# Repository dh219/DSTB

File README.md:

## David's ST Booster (DSTB)

# WARNING 27 July 2024 #

I strongly recommend no new builds of this project for now. I believe there's a reliabiltiy of executing from AltRAM which I've not been able to get to the bottom of.

Memory tests pass reliably, but I think the approach to this design in combination with clock switching and attempting to service DMA is inherently flawed.

Unless I find a firmware fix, in which case I'll log that here, I recommend persuing other designs or waiting for a revision 2.

David.

---

#### A low-cost DIY 16MHz 68000 accelerator with 8MB fast AltRAM and optional ROM cacheing

Fitting into a small footprint, just 3mm wider than the 68000 socket into which this plugs, the board (\~$4) contains one XC95144XL-100 CPLD (\~$5), one 32Mbit TSSOP-II-54 SDRAM chip (~$5), two level-shifting buffers (\~$6), one 5 or 3.3V 66MHz oscillator in a 7x5mm package (\~$4) and a 3.3V LDO voltage regulator (\~$2) as the core components.

This provides all the interface between the ST and a 16MHz capable 68000. The 68000 will run at the oscillator frequency divided by four, so 16.5MHz in normal configuration.

The AltRAM runs at at full speed for a 16MHz processor, offering throughput of around 7.7MB/s compared to ST-RAM's 3.7MB/s.

Firmware source (ISE), board design files (KiCAD) and any source for support programs will be published at each release.

#### Cost & requirements

I anticipate a single board can be hand assembled for approximately 30USD. You may need to acquire a 16MHz capable DIP-64 68000 to pair with it if your old 8MHz chip cannot handle the faster clock.

#### Manual

At the moment, there is no manual. This will be written in due course.

There is a build video available at https://youtu.be/VHx3kat0Q6M

### Resistor Networks

All resistor networks are recommended, however if you have already carried out preventative maintenance on your ST board such that the bus resistor packs have been changed to 2k2 or lower, you may omit the resistor packs on the address and data bus (RN1-10).

Please note, RN11 is not a supplementary bus pull-up pack and is required for correct operation of the firmware.

#### Software

See https://github.com/dh219/DSTB-tools for the 'AltRAM' or 'AltROM' programs (NB. 'AltROM' hasn't been properly tested with later firmware builds & this board is not compatible with 'ExxosRAM.PRG').

EmuTOS automatically recognises and activate AltRAM.

---

*Copyright 2022 D Henderson, released under GPL2.0*

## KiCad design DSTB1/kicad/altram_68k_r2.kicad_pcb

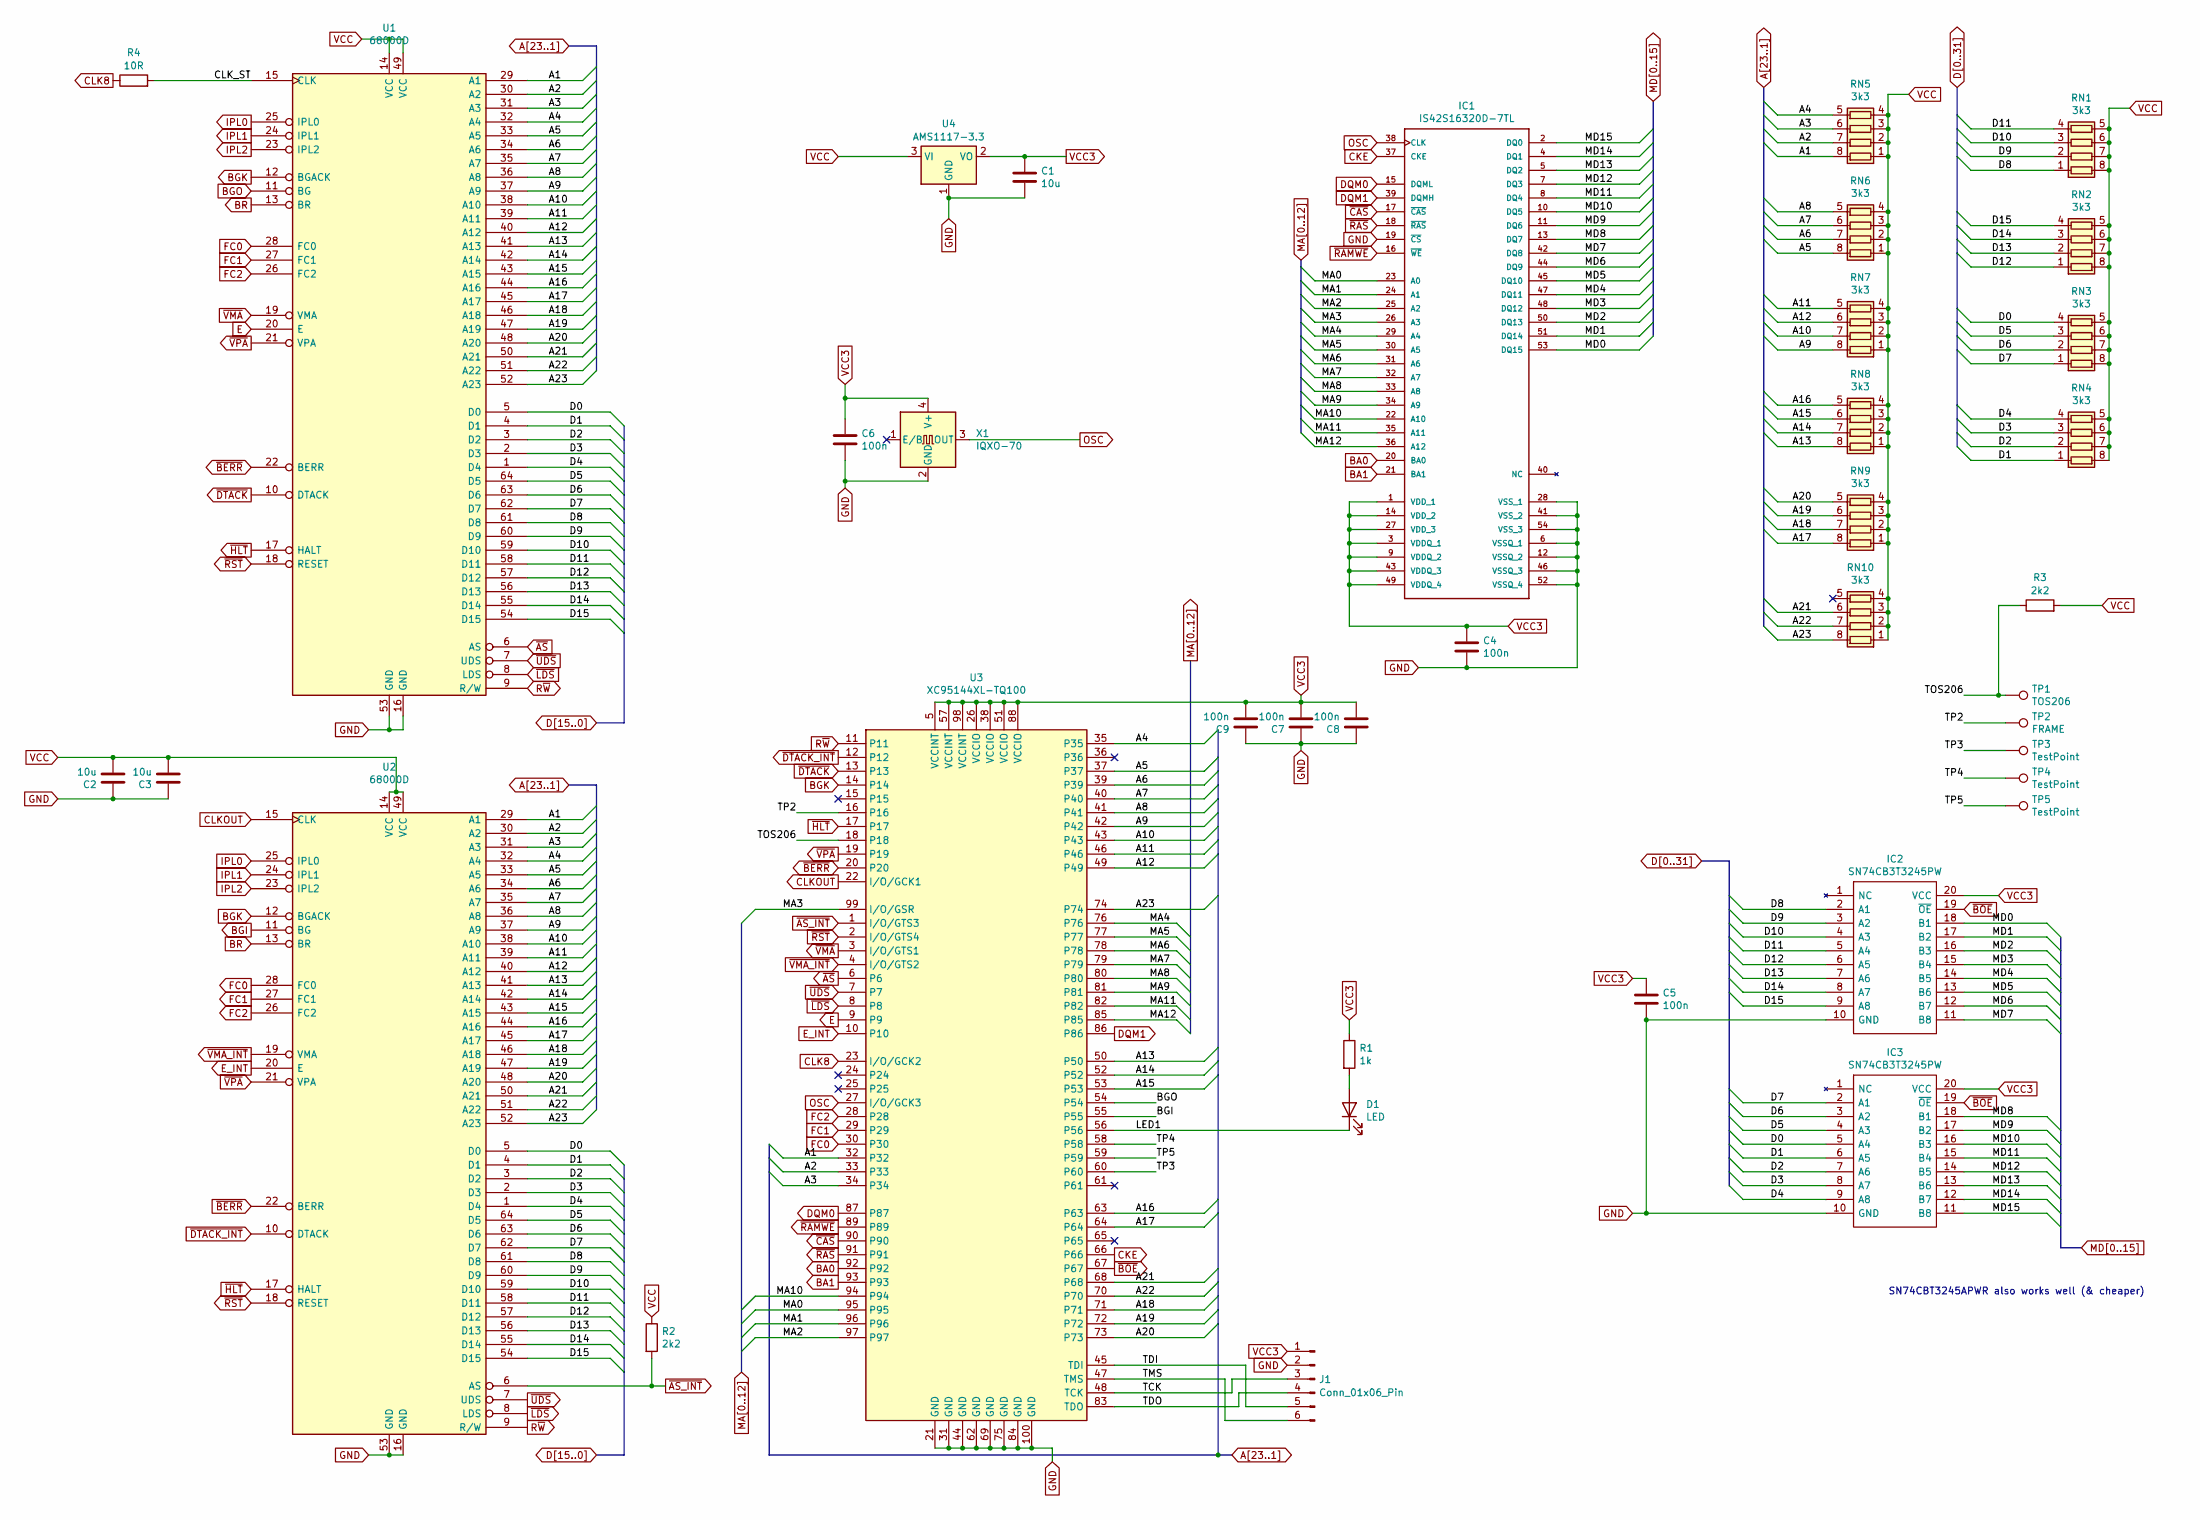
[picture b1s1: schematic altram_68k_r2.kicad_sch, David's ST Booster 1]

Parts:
C1, C2, C3: 10u; C_0805_2012Metric_Pad1.18x1.45mm_HandSolder
C4, C5, C6, C7, C8, C9: 100n; C_0805_2012Metric_Pad1.18x1.45mm_HandSolder
D1: LED; LED_0805_2012Metric_Pad1.15x1.40mm_HandSolder
IC1: IS42S16320D-7TL; TSOP-II-54_22.2x10.16mm_P0.8mm; MANUFACTURER_PART_NUMBER IS42S16320D-7TL
IC2, IC3: SN74CB3T3245PW; TSSOP-20_4.4x6.5mm_P0.65mm; Manufacturer_Part_Number SN74CB3T3245DW; Mouser Part Number 595-SN74CB3T3245DW
J1: Conn_01x06_Pin; PinHeader_1x06_P2.54mm_Horizontal
R1: 1k; R_0805_2012Metric_Pad1.20x1.40mm_HandSolder
R2, R3: 2k2; R_0805_2012Metric_Pad1.20x1.40mm_HandSolder
R4: 10R; R_0805_2012Metric_Pad1.20x1.40mm_HandSolder
RN1, RN2, RN3, RN4, RN5, RN6, RN7, RN8, RN9, RN10: 3k3; R_Array_Convex_4x0603
TP1: TOS206; TestPoint_THTPad_1.0x1.0mm_Drill0.5mm
TP2: FRAME; TestPoint_THTPad_1.0x1.0mm_Drill0.5mm
TP3, TP4, TP5: TestPoint; TestPoint_THTPad_1.0x1.0mm_Drill0.5mm
U1: 68000D; DIP-64_W22.86mm
U2: 68000D; DIP-64_W22.86mm_Socket
U3: XC95144XL-TQ100; TQFP-100_14x14mm_P0.5mm
U4: AMS1117-3.3; SOT-223-3_TabPin2
X1: IQXO-70; Oscillator_SMD_IQD_IQXO70-4Pin_7.5x5.0mm

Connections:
/CLK_ST: R4.2, U1.15 (CLK)
/LED1: D1.1 (K), U3.56
/TCK: J1.3, U3.48 (TCK)
/TDI: J1.5, U3.45 (TDI)
/TDO: J1.4, U3.83 (TDO)
/TMS: J1.6, U3.47 (TMS)
/TOS206: R3.1, TP1.1, U3.18
/TP2: TP2.1, U3.16
/TP3: TP3.1, U3.60
/TP4: TP4.1, U3.58
/TP5: TP5.1, U3.59
A1: RN5.8 (R1.2), U1.29 (A1), U2.29 (A1), U3.32
A2: RN5.7 (R2.2), U1.30 (A2), U2.30 (A2), U3.33
A3: RN5.6 (R3.2), U1.31 (A3), U2.31 (A3), U3.34
A4: RN5.5 (R4.2), U1.32 (A4), U2.32 (A4), U3.35
A5: RN6.8 (R1.2), U1.33 (A5), U2.33 (A5), U3.37
A6: RN6.7 (R2.2), U1.34 (A6), U2.34 (A6), U3.39
A7: RN6.6 (R3.2), U1.35 (A7), U2.35 (A7), U3.40
A8: RN6.5 (R4.2), U1.36 (A8), U2.36 (A8), U3.41
A9: RN7.8 (R1.2), U1.37 (A9), U2.37 (A9), U3.42
A10: RN7.7 (R2.2), U1.38 (A10), U2.38 (A10), U3.43
A11: RN7.5 (R4.2), U1.39 (A11), U2.39 (A11), U3.46
A12: RN7.6 (R3.2), U1.40 (A12), U2.40 (A12), U3.49
A13: RN8.8 (R1.2), U1.41 (A13), U2.41 (A13), U3.50
A14: RN8.7 (R2.2), U1.42 (A14), U2.42 (A14), U3.52
A15: RN8.6 (R3.2), U1.43 (A15), U2.43 (A15), U3.53
A16: RN8.5 (R4.2), U1.44 (A16), U2.44 (A16), U3.63
A17: RN9.8 (R1.2), U1.45 (A17), U2.45 (A17), U3.64
A18: RN9.7 (R2.2), U1.46 (A18), U2.46 (A18), U3.71
A19: RN9.6 (R3.2), U1.47 (A19), U2.47 (A19), U3.72
A20: RN9.5 (R4.2), U1.48 (A20), U2.48 (A20), U3.73
A21: RN10.6 (R3.2), U1.50 (A21), U2.50 (A21), U3.68
A22: RN10.7 (R2.2), U1.51 (A22), U2.51 (A22), U3.70
A23: RN10.8 (R1.2), U1.52 (A23), U2.52 (A23), U3.74
BA0: IC1.20 (BA0), U3.92
BA1: IC1.21 (BA1), U3.93
BGI: U2.11 (BG), U3.55
BGK: U1.12 (BGACK), U2.12 (BGACK), U3.14
BGO: U1.11 (BG), U3.54
BR: U1.13 (BR), U2.13 (BR)
CKE: IC1.37 (CKE), U3.66
CLK8: R4.1, U3.23 (I/O/GCK2)
CLKOUT: U2.15 (CLK), U3.22 (I/O/GCK1)
D0: IC3.5 (A4), RN3.4 (R4.1), U1.5 (D0), U2.5 (D0)
D1: IC3.6 (A5), RN4.1 (R1.1), U1.4 (D1), U2.4 (D1)
D2: IC3.7 (A6), RN4.2 (R2.1), U1.3 (D2), U2.3 (D2)
D3: IC3.8 (A7), RN4.3 (R3.1), U1.2 (D3), U2.2 (D3)
D4: IC3.9 (A8), RN4.4 (R4.1), U1.1 (D4), U2.1 (D4)
D5: IC3.4 (A3), RN3.3 (R3.1), U1.64 (D5), U2.64 (D5)
D6: IC3.3 (A2), RN3.2 (R2.1), U1.63 (D6), U2.63 (D6)
D7: IC3.2 (A1), RN3.1 (R1.1), U1.62 (D7), U2.62 (D7)
D8: IC2.2 (A1), RN1.1 (R1.1), U1.61 (D8), U2.61 (D8)
D9: IC2.3 (A2), RN1.2 (R2.1), U1.60 (D9), U2.60 (D9)
D10: IC2.4 (A3), RN1.3 (R3.1), U1.59 (D10), U2.59 (D10)
D11: IC2.5 (A4), RN1.4 (R4.1), U1.58 (D11), U2.58 (D11)
D12: IC2.6 (A5), RN2.1 (R1.1), U1.57 (D12), U2.57 (D12)
D13: IC2.7 (A6), RN2.2 (R2.1), U1.56 (D13), U2.56 (D13)
D14: IC2.8 (A7), RN2.3 (R3.1), U1.55 (D14), U2.55 (D14)
D15: IC2.9 (A8), RN2.4 (R4.1), U1.54 (D15), U2.54 (D15)
DQM0: IC1.15 (DQML), U3.87
DQM1: IC1.39 (DQMH), U3.86
E: U1.20 (E), U3.9
E_INT: U2.20 (E), U3.10
FC0: U1.28 (FC0), U2.28 (FC0), U3.30
FC1: U1.27 (FC1), U2.27 (FC1), U3.29
FC2: U1.26 (FC2), U2.26 (FC2), U3.28
GND: C1.2, C2.1, C3.1, C4.2, C5.2, C6.2, C7.1, C8.1, C9.1, IC1.6 (VSSQ_1), IC1.12 (VSSQ_2), IC1.19 (~CS), IC1.28 (VSS_1), IC1.41 (VSS_2), IC1.46 (VSSQ_3), IC1.52 (VSSQ_4), IC1.54 (VSS_3), IC2.10 (GND), IC3.10 (GND), J1.2, U1.16 (GND), U1.53 (GND), U2.16 (GND), U2.53 (GND), U3.21 (GND), U3.31 (GND), U3.44 (GND), U3.62 (GND), U3.69 (GND), U3.75 (GND), U3.84 (GND), U3.100 (GND), U4.1 (GND), X1.2 (GND)
IPL0: U1.25 (IPL0), U2.25 (IPL0)
IPL1: U1.24 (IPL1), U2.24 (IPL1)
IPL2: U1.23 (IPL2), U2.23 (IPL2)
MA0: IC1.23 (A0), U3.95
MA1: IC1.24 (A1), U3.96
MA2: IC1.25 (A2), U3.97
MA3: IC1.26 (A3), U3.99 (I/O/GSR)
MA4: IC1.29 (A4), U3.76
MA5: IC1.30 (A5), U3.77
MA6: IC1.31 (A6), U3.78
MA7: IC1.32 (A7), U3.79
MA8: IC1.33 (A8), U3.80
MA9: IC1.34 (A9), U3.81
MA10: IC1.22 (A10), U3.94
MA11: IC1.35 (A11), U3.82
MA12: IC1.36 (A12), U3.85
MD0: IC1.53 (DQ15), IC2.18 (B1)
MD1: IC1.51 (DQ14), IC2.17 (B2)
MD2: IC1.50 (DQ13), IC2.16 (B3)
MD3: IC1.48 (DQ12), IC2.15 (B4)
MD4: IC1.47 (DQ11), IC2.14 (B5)
MD5: IC1.45 (DQ10), IC2.13 (B6)
MD6: IC1.44 (DQ9), IC2.12 (B7)
MD7: IC1.42 (DQ8), IC2.11 (B8)
MD8: IC1.13 (DQ7), IC3.18 (B1)
MD9: IC1.11 (DQ6), IC3.17 (B2)
MD10: IC1.10 (DQ5), IC3.16 (B3)
MD11: IC1.8 (DQ4), IC3.15 (B4)
MD12: IC1.7 (DQ3), IC3.14 (B5)
MD13: IC1.5 (DQ2), IC3.13 (B6)
MD14: IC1.4 (DQ1), IC3.12 (B7)
MD15: IC1.2 (DQ0), IC3.11 (B8)
unnamed: D1.2 (A), R1.2
OSC: IC1.38 (CLK), U3.27 (I/O/GCK3), X1.3 (OUT)
R~W: U1.9 (R/W), U2.9 (R/W), U3.11
VCC: C2.2, C3.2, R2.1, R3.2, RN1.5 (R4.2), RN1.6 (R3.2), RN1.7 (R2.2), RN1.8 (R1.2), RN2.5 (R4.2), RN2.6 (R3.2), RN2.7 (R2.2), RN2.8 (R1.2), RN3.5 (R4.2), RN3.6 (R3.2), RN3.7 (R2.2), RN3.8 (R1.2), RN4.5 (R4.2), RN4.6 (R3.2), RN4.7 (R2.2), RN4.8 (R1.2), RN5.1 (R1.1), RN5.2 (R2.1), RN5.3 (R3.1), RN5.4 (R4.1), RN6.1 (R1.1), RN6.2 (R2.1), RN6.3 (R3.1), RN6.4 (R4.1), RN7.1 (R1.1), RN7.2 (R2.1), RN7.3 (R3.1), RN7.4 (R4.1), RN8.1 (R1.1), RN8.2 (R2.1), RN8.3 (R3.1), RN8.4 (R4.1), RN9.1 (R1.1), RN9.2 (R2.1), RN9.3 (R3.1), RN9.4 (R4.1), RN10.1 (R1.1), RN10.2 (R2.1), RN10.3 (R3.1), RN10.4 (R4.1), U1.14 (VCC), U1.49 (VCC), U2.14 (VCC), U2.49 (VCC), U4.3 (VI)
VCC3: C1.1, C4.1, C5.1, C6.1, C7.2, C8.2, C9.2, IC1.1 (VDD_1), IC1.3 (VDDQ_1), IC1.9 (VDDQ_2), IC1.14 (VDD_2), IC1.27 (VDD_3), IC1.43 (VDDQ_3), IC1.49 (VDDQ_4), IC2.20 (VCC), IC3.20 (VCC), J1.1, R1.1, U3.5 (VCCINT), U3.26 (VCCIO), U3.38 (VCCIO), U3.51 (VCCIO), U3.57 (VCCINT), U3.88 (VCCIO), U3.98 (VCCINT), U4.2 (VO), X1.4 (V+)
~AS_INT: R2.2, U2.6 (AS), U3.1 (I/O/GTS3)
~AS: U1.6 (AS), U3.6
~BERR: U1.22 (BERR), U2.22 (BERR), U3.20
~BOE: IC2.19 (~OE), IC3.19 (~OE), U3.67
~CAS: IC1.17 (~CAS), U3.90
~DTACK_INT: U2.10 (DTACK), U3.12
~DTACK: U1.10 (DTACK), U3.13
~HLT: U1.17 (HALT), U2.17 (HALT), U3.17
~LDS: U1.8 (LDS), U2.8 (LDS), U3.8
~RAMWE: IC1.16 (~WE), U3.89
~RAS: IC1.18 (~RAS), U3.91
~RST: U1.18 (RESET), U2.18 (RESET), U3.2 (I/O/GTS4)
~UDS: U1.7 (UDS), U2.7 (UDS), U3.7
~VMA_INT: U2.19 (VMA), U3.4 (I/O/GTS2)
~VMA: U1.19 (VMA), U3.3 (I/O/GTS1)
~VPA: U1.21 (VPA), U2.21 (VPA), U3.19

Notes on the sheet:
SN74CBT3245APWR also works well (& cheaper)

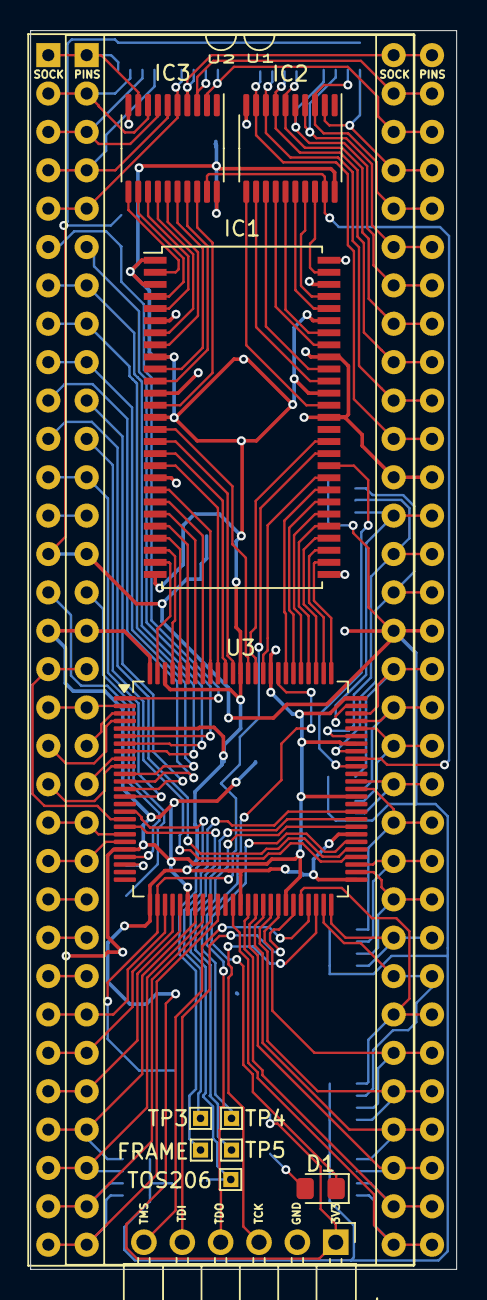
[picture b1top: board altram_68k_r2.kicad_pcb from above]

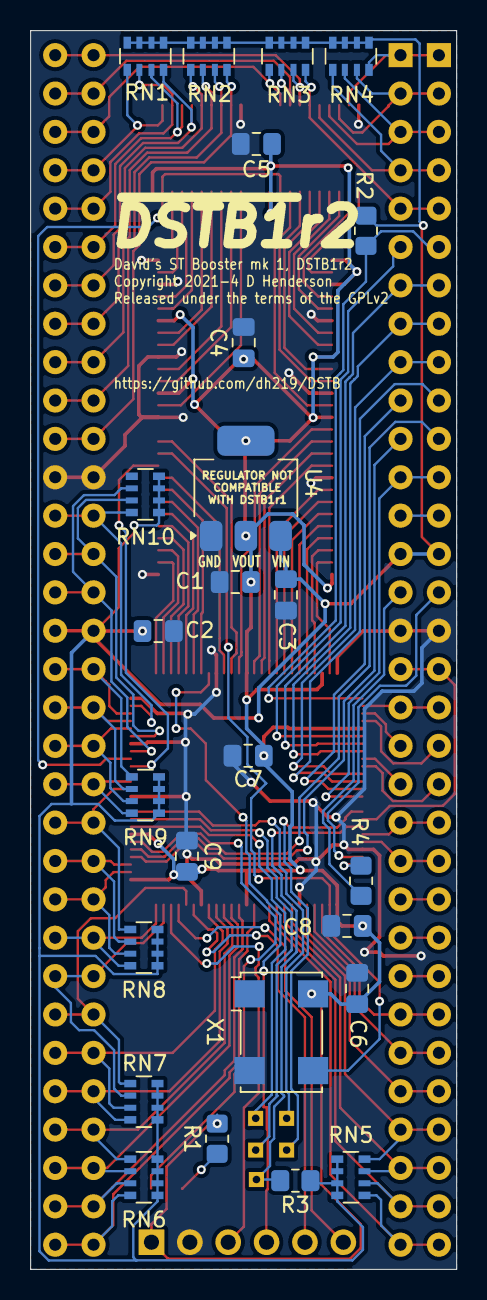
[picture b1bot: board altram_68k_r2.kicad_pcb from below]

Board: 2 copper layers, 28.2 x 82.0 mm, 38 parts (25 on the bottom side), 120 nets.

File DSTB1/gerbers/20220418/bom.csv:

Comment,Designator,Footprint,LCSC Part #
100n Unpolarized capacitor,"C1,C3,C5,C7,C9",C_0805_2012Metric_Pad1.18x1.45mm_HandSolder,
10u Unpolarized capacitor,"C4,C8,C10",C_0805_2012Metric_Pad1.18x1.45mm_HandSolder,
LED Light emitting diode,D1,LED_0805_2012Metric_Pad1.15x1.40mm_HandSolder,
IS42S16320D-7TL ,IC1,TSOP-II-54_22.2x10.16mm_P0.8mm,
"SN74CB3T3245PW Texas Instruments SN74CB3T3245DW, Bus Switch, 8 x 1:1, 2.3  3.6 V, 20-Pin SOIC","IC2,IC3",TSSOP-20_4.4x6.5mm_P0.65mm,C7145
"Conn_01x06_Male Generic connector, single row, 01x06, script generated (kicad-library-utils/schlib/autogen/connector/)",J1,PinHeader_1x06_P2.54mm_Horizontal,
1k Resistor,R1,R_0805_2012Metric_Pad1.20x1.40mm_HandSolder,
2k2 Resistor,R2,C_0805_2012Metric_Pad1.18x1.45mm_HandSolder,
"3k3 4 resistor network, parallel topology","RN1,RN2,RN3,RN4,RN5,RN6,RN7,RN8,RN9,RN10,RN11",R_Array_Convex_4x0603,
68000D 16/32-bit Microprocessor,U1,DIP-64_W22.86mm,
68000D 16/32-bit Microprocessor,U2,DIP-64_W22.86mm_Socket,
"XC95144XL-TQ100 CPLD, 144 Macrocells, 3200 Usable Gates",U3,TQFP-100_14x14mm_P0.5mm,
"LT1129-3.3_SOT223 700mA Micropower Low drop-out regulator, Fixed Output 3.3V, SOT-223",U4,SOT-223-3_TabPin2,
"IQXO-70 Crystal Clock Oscillator, SMD package 7.5x5.0mm²",X1,Oscillator_SMD_IQD_IQXO70-4Pin_7.5x5.0mm,

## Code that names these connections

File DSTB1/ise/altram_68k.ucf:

#r2 
#NET CKE  LOC = "P40"; # dropped in r2
#Created by Constraints Editor (xc95144xl-tq100-10) - 2022/05/10
NET "CLKOSC" TNM_NET = CLKOSC;
NET "CLK8" TNM_NET = CLK8;
#PACE: Start of Constraints generated by PACE
NET "CLKOUT" TNM_NET = CLKOUT;

#PACE: Start of PACE I/O Pin Assignments
NET "A<10>"  LOC = "P43"  ; 
NET "A<11>"  LOC = "P46"  ; 
NET "A<12>"  LOC = "P49"  ; 
NET "A<13>"  LOC = "P50"  ; 
NET "A<14>"  LOC = "P52"  ; 
NET "A<15>"  LOC = "P53"  ; 
NET "A<16>"  LOC = "P63"  ; 
NET "A<17>"  LOC = "P64"  ; 
NET "A<18>"  LOC = "P71"  ; 
NET "A<19>"  LOC = "P72"  ; 
NET "A<1>"  LOC = "P32"  ; 
NET "A<20>"  LOC = "P73"  ; 
NET "A<21>"  LOC = "P68"  ; 
NET "A<22>"  LOC = "P70"  ; 
NET "A<23>"  LOC = "P74"  ; 
NET "A<2>"  LOC = "P33"  ; 
NET "A<3>"  LOC = "P34"  ; 
NET "A<4>"  LOC = "P35"  ; 
NET "A<5>"  LOC = "P37"  ; 
NET "A<6>"  LOC = "P39"  ; 
NET "A<7>"  LOC = "P40"  ; 
NET "A<8>"  LOC = "P41"  ; 
NET "A<9>"  LOC = "P42"  ; 
NET "AS"  LOC = "P6"  ; 
NET "AS_INT"  LOC = "P1"  ; 
NET "BA<0>"  LOC = "P92"  ; 
NET "BA<1>"  LOC = "P93"  ; 
NET "BERR"  LOC = "P20"  ; 
NET "BGK"  LOC = "P14"  ; 
NET "BOE"  LOC = "P67"  ; 
NET "CAS"  LOC = "P90"  ; 
NET "CLK8"  LOC = "P23" |BUFG = CLK ; 
NET "CLKOSC_OLD"  LOC = "P36"  ; 
NET "CLKOUT"  LOC = "P22"  ; 
NET "DQM<0>"  LOC = "P87"  ; 
NET "DQM<1>"  LOC = "P86"  ; 
NET "DTACK"  LOC = "P13"  ; 
NET "DTACK_INT"  LOC = "P12"  ; 
NET "E"  LOC = "P9"  ; 
NET "E_INT"  LOC = "P10"  ; 
NET "FC<0>"  LOC = "P30"  ; 
NET "FC<1>"  LOC = "P29"  ; 
NET "FC<2>"  LOC = "P28"  ; 
NET "LDS"  LOC = "P8"  ; 
NET "LED"  LOC = "P56"  ; 
NET "MA<0>"  LOC = "P95"  ; 
NET "MA<10>"  LOC = "P94"  ; 
NET "MA<11>"  LOC = "P82"  ; 
NET "MA<12>"  LOC = "P85"  ; 
NET "MA<1>"  LOC = "P96"  ; 
NET "MA<2>"  LOC = "P97"  ; 
NET "MA<3>"  LOC = "P99"  ; 
NET "MA<4>"  LOC = "P76"  ; 
NET "MA<5>"  LOC = "P77"  ; 
NET "MA<6>"  LOC = "P78"  ; 
NET "MA<7>"  LOC = "P79"  ; 
NET "MA<8>"  LOC = "P80"  ; 
NET "MA<9>"  LOC = "P81"  ; 
NET "CLKOSC"  LOC = "P27" | BUFG = CLK ; 
NET "RAMWE"  LOC = "P89"  ; 
NET "RAS"  LOC = "P91"  ; 
NET "RST"  LOC = "P2"  ; 
NET "RW"  LOC = "P11"  ; 
NET "TP<1>"  LOC = "P18"  ; 
NET "TP<2>"  LOC = "P17"  ; 
NET "TP<3>"  LOC = "P66"  ; 
NET "TP<4>"  LOC = "P54"  ; 
NET "TP<5>"  LOC = "P55"  ; 
NET "UDS"  LOC = "P7"  ; 
NET "VMA"  LOC = "P3"  ; 
NET "VMA_INT"  LOC = "P4"  ; 
NET "VPA"  LOC = "P19"  ; 

#PACE: Start of PACE Area Constraints
#PACE: Start of PACE Prohibit Constraints
#PACE: End of Constraints generated by PACE
#Created by Constraints Editor (xc95144xl-tq100-10) - 2024/07/23
TIMESPEC TS_CLKOSC = PERIOD "CLKOSC" 66 MHz HIGH 50%;
#Created by Constraints Editor (xc95144xl-tq100-10) - 2024/07/23


#NET "CLK_D<1>" TNM_NET = CLK_D;
#TIMESPEC TS_CLK_D = PERIOD "CLK_D" 66 MHz HIGH 50%;
#NET "CLKOSC_2" TNM_NET = CLKOSC_2;
#TIMESPEC TS_CLKOSC_2 = PERIOD "CLKOSC_2" 33 MHz HIGH 50%;
#NET "CLKOSC_4" TNM_NET = CLKOSC_4;
#TIMESPEC TS_CLKOSC_4 = PERIOD "CLKOSC_4" 16.5 MHz HIGH 50%;

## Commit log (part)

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2022-04-18 Seeding the build files + verilog for DSTB1. Kicad to follow once libraries are sorted out.
2022-04-19 Adding Kicad 5 files for the release version
2022-05-07 Hacked for TOS206 decoding and staying at 8MHz for testing AltRAM at different speeds
2022-05-10 Simplified state machine; speculative fix for RMW.
2022-05-10 SCratch the last one. This one tries to avoid RMW problems
2022-05-10 Registering the altram output
2022-05-10 Changed the timer to work on the 66MHz osc
2022-05-10 Reducing flipflops slowly
2022-05-10 Reducing flipflops as best as possible -- any further and we don't fit
2022-05-10 Attempts made to stop the state machine tripping over itself at 8MHz. Read failing on occasion. Check read term logic.
2022-05-12 registering the async inputs -- seems to work at 8MHz too. RMW not handled.
2022-05-13 Attempt to sort out the PSG DTACK bug in ST(F)(M)s
2022-05-24 Quick hack to support RMW at the expense of AltRAM speed to test stability on H5 boards.
2022-05-24 Inverting 8MHz/16MHz logic as reported working on H5 board
2022-05-31 Adding missing library dependencies
2022-05-31 Added new 'stable' JEDEC file
2022-06-13 Resistor network requirement clarification.
2023-10-17 Fixed TOS206 decode to honour blitter requests too.
2024-06-27 Adding missing symbol
2024-06-27 Update README.md
    DSTB1 should be considered end of life
2024-07-01 Working on a CKE-enabled SDRAM system using TP[1] and a hacked board.
2024-07-12 Much changes. Passing tests. Inefficent & running at 16MHz.
2024-07-15 Back to pretty much where we started. Passing all tests. Not all programs stable. Time to simplify.
2024-07-23 Trying out the SJ Leary Invert, Sample and Delay clock reconstruction technique. Also added extra time constraints. Needing a BR sensing line too.
2024-07-24 Added support for the new BGI and BGO lines. Repositioned TOS206 decoder to match last release
2024-07-25 Seems stable on STE and STFM (adding in the PSG delay)
2024-07-26 Tidying up some naming for possibly supporting blitter
2024-07-28 Tiding up some clock terminology -- interesting result on blitter work
2024-07-28 Added video counter again
2024-08-02 I've been unable to get blitter access working again. Line F errors and invalid instruction errors about in 16MHz mode. Unfortunately I lost my almost working code, so this is a partial commit to not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
2024-08-04 Just tidying up some clock calculations to hopefully reduce jitter
2024-08-05 Blitter access nearly perfect (on one card -- second card has issues) with some extremly experimental delay/non-delay code.
2024-08-06 Really really hacky attempt to avoid access<-->access delays. Not 100% kosher.
2024-08-08 Adding more synchronisers. Possibly overdone it as blitter access causes bombs again.
2024-08-08 Decided to use a new register base to stop pretending to be a Monster card.
2024-08-08 Going around in circles with blitter access. I think the synchronisers, or perhaps the simulated clock is the problem. This version asserts BERR and fails to blit. At least it's not crashing (yet!)
2024-08-12 Current state of play has reads at 7.7MB/s but writes down at 5.
2024-08-12 Realised that by testing VALID against DS_IN I was having to go around the write cycle at least twice. Changing to AS_IN as the deassert trigger has taken the write speed up to over 7 MB/s
2024-08-12 Correcting the other latch options too
2024-08-12 Tiding up a bit. Given up with blitter for now. Need to react faster -- clever synchronisers don't cut it.
2024-08-15 Added an AltROM detect register and a cold boot flag.
2024-08-16 Using old RAMCLK input as the CLKOSC now
2024-08-16 Experimental change to the SDRAM trigger mechanism to have it edge-based rather than level-based. Re-enabled blitter support to test Ijor's theory of 'twice around'.
2024-08-20 Working on the refactor for rev2
2024-08-21 No DRC fails. All symbols updated. Bit of ground stitching.
2024-08-21 minor timespec mod
2024-08-21 Trying a faster BGO offering if not using altram. Doing away with long baseline timespecs (may be a bad idea)
2024-08-26 Speed optimisation possible with BG hold off logic change
2024-08-26 Back to using the old clock technique to test reliability on Andre's machines.
2024-08-27 Adding an inline termination to the clk8 line, just in case.
2024-09-11 Added support for HALT on TP[2], but didn't find a use.
2024-09-20 Rejigged the bottom a bit to provide a better ground plane. Changed to the 1117-3.3 regulator
2024-09-20 Moved osc to the bottom layer and reworked traces for better ground plane for most of the board. Strapping added for two caps on the more isolated side.

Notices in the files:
DSTB1/kicad/altram_68k_r2.kicad_pcb:
Copyright 2021-4 D Henderson
Released under the terms of the GPLv2
